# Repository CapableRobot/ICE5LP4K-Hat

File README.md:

# ICE5LP4K-Hat

## System Setup 

```
cd loader
make
cd ..

mkdir install
cd install
wget https://raw.githubusercontent.com/enjoy-digital/litex/master/litex_setup.py
chmod +x litex_setup.py
./litex_setup.py init install --user 

pip3 install spidev
```

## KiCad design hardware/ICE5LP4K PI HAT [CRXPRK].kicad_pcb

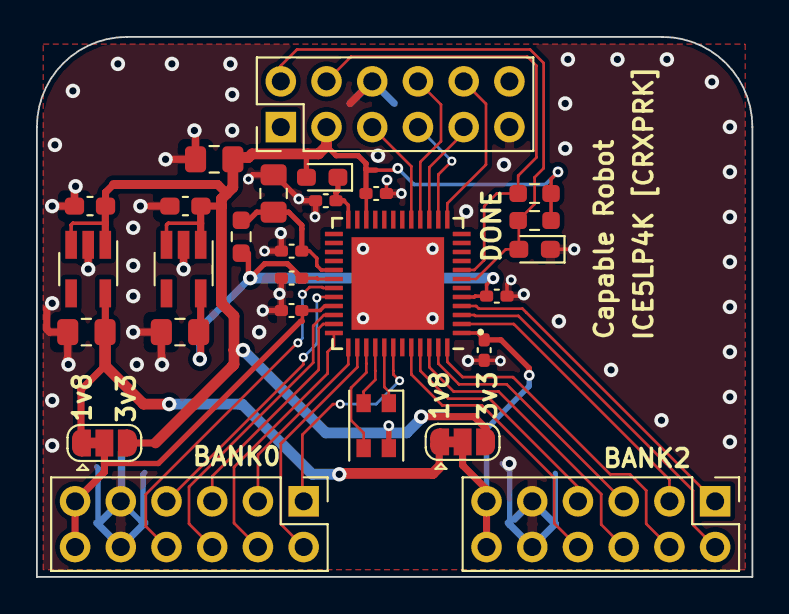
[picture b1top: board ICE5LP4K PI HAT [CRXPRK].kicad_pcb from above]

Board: 2 copper layers, 39.8 x 30.0 mm, 27 parts (0 on the bottom side), 34 nets.

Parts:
C1, C302: 1uf; C_0603_1608Metric_Pad1.08x0.95mm_HandSolder
C2, C303, C304, C406: 10uf; C_0805_2012Metric_Pad1.18x1.45mm_HandSolder
C401, C402, C403, C404, C405, C407, C408: 0.1uf; C_0402_1005Metric_Pad0.74x0.62mm_HandSolder
D401: LED; LED_0603_1608Metric_Pad1.05x0.95mm_HandSolder
D405: D; D_0603_1608Metric_Pad1.05x0.95mm_HandSolder
J1, J2, J3: Conn_02x06_Odd_Even; PinHeader_2x06_P2.54mm_Vertical
JP1, JP2: Jumper_3_Bridged12; SolderJumper-3_P1.3mm_Bridged12_RoundedPad1.0x1.5mm
R401: 10k; R_0603_1608Metric_Pad0.98x0.95mm_HandSolder
R402: 2.2k; R_0603_1608Metric_Pad0.98x0.95mm_HandSolder
R406: 100; R_0603_1608Metric_Pad0.98x0.95mm_HandSolder
RGB1: LED_RGBA; LED_Cree-PLCC4_3.2x2.8mm_CCW
U1: MCP1824-1.8; SOT-23-5_HandSoldering
U302: MCP1824-1.2; SOT-23-5_HandSoldering
U401: ice5lp4k_sg48; QFN-48-1EP_7x7mm_Pitch0.5mm_DIY_PADS

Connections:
+1V2: C304.1, C402.1, C407.1, R406.2, U302.5, U401.5, U401.30
+1V8: C2.1, JP1.1, JP2.1, U1.5
+3V3: C1.1, C302.1, C303.1, C404.1, D405.2, J1.3, JP1.3, JP2.3, R401.1, R402.1, RGB1.4, U1.1, U1.3, U302.1, U302.3, U401.22
/FPGA/B_0a: J2.6, U401.46
/FPGA/B_2a: J2.5, U401.47
/FPGA/B_3b: J2.8, U401.44
/FPGA/B_4a: J2.4, U401.48
/FPGA/B_5a: J2.7, U401.45
/FPGA/B_6a: J2.3, U401.2
/FPGA/B_8a: J2.1, U401.4
/FPGA/B_9a: J2.2, U401.3
/FPGA/VCCIO_0: C408.1, J3.11, J3.12, JP2.2, U401.33
/FPGA/VCCIO_2: C401.1, J2.11, J2.12, JP1.2, U401.1
/FPGA/VCCPLL: C405.1, C406.1, R406.1, U401.29
GND: C1.2, C2.2, C302.2, C303.2, C304.2, C401.2, C402.2, C403.2, C404.2, C405.2, C406.2, C407.2, C408.2, D401.1, J1.6, J1.11, J2.9, J2.10, J3.9, J3.10, U1.2, U302.2, U401.49
GPIO23_CDN: D401.2, J1.2, R402.2, U401.7
GPIO24_CRS: J1.4, R401.2, U401.8
GPIO25_SS: J1.8, U401.16
unnamed: C403.1, D405.1, U401.24
unnamed: J3.1, U401.42
unnamed: J3.2, U401.38
unnamed: J3.3, U401.37
unnamed: J3.4, U401.36
unnamed: J3.5, U401.35
unnamed: J3.6, U401.34
unnamed: J3.7, U401.32
unnamed: J3.8, U401.31
unnamed: RGB1.1, U401.41
unnamed: RGB1.2, U401.40
unnamed: RGB1.3, U401.39
SPI_CE0: J1.10, U401.13
SPI_CLK: J1.9, U401.15
SPI_MISO: J1.7, U401.14
SPI_MOSI: J1.5, U401.17

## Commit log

2021-10-08 Add open-source FPGA bitstream loader
2021-10-08 Add litex-based FPGA trigger gateware
2021-10-08 Add CLI control interface (python)
2021-10-08 Change location of generated csr.csv file
2021-10-08 Initial install instructions
2021-10-08 Update ignore
2021-10-15 Reduce RGB LED current and fix CSR r/w issue
2021-10-15 Add RGB LEDs to CSR
2021-10-15 Copy generated csr.csv and bin file into folder for archive and use by CLI
2021-10-15 Allow for name based CSR lookup and hex, binary, and decimal formating of inputs
2021-10-15 Update ignore file for KICAD
2021-10-15 Add hardware design
2021-10-15 Adding schematic PDF and PCB renders
